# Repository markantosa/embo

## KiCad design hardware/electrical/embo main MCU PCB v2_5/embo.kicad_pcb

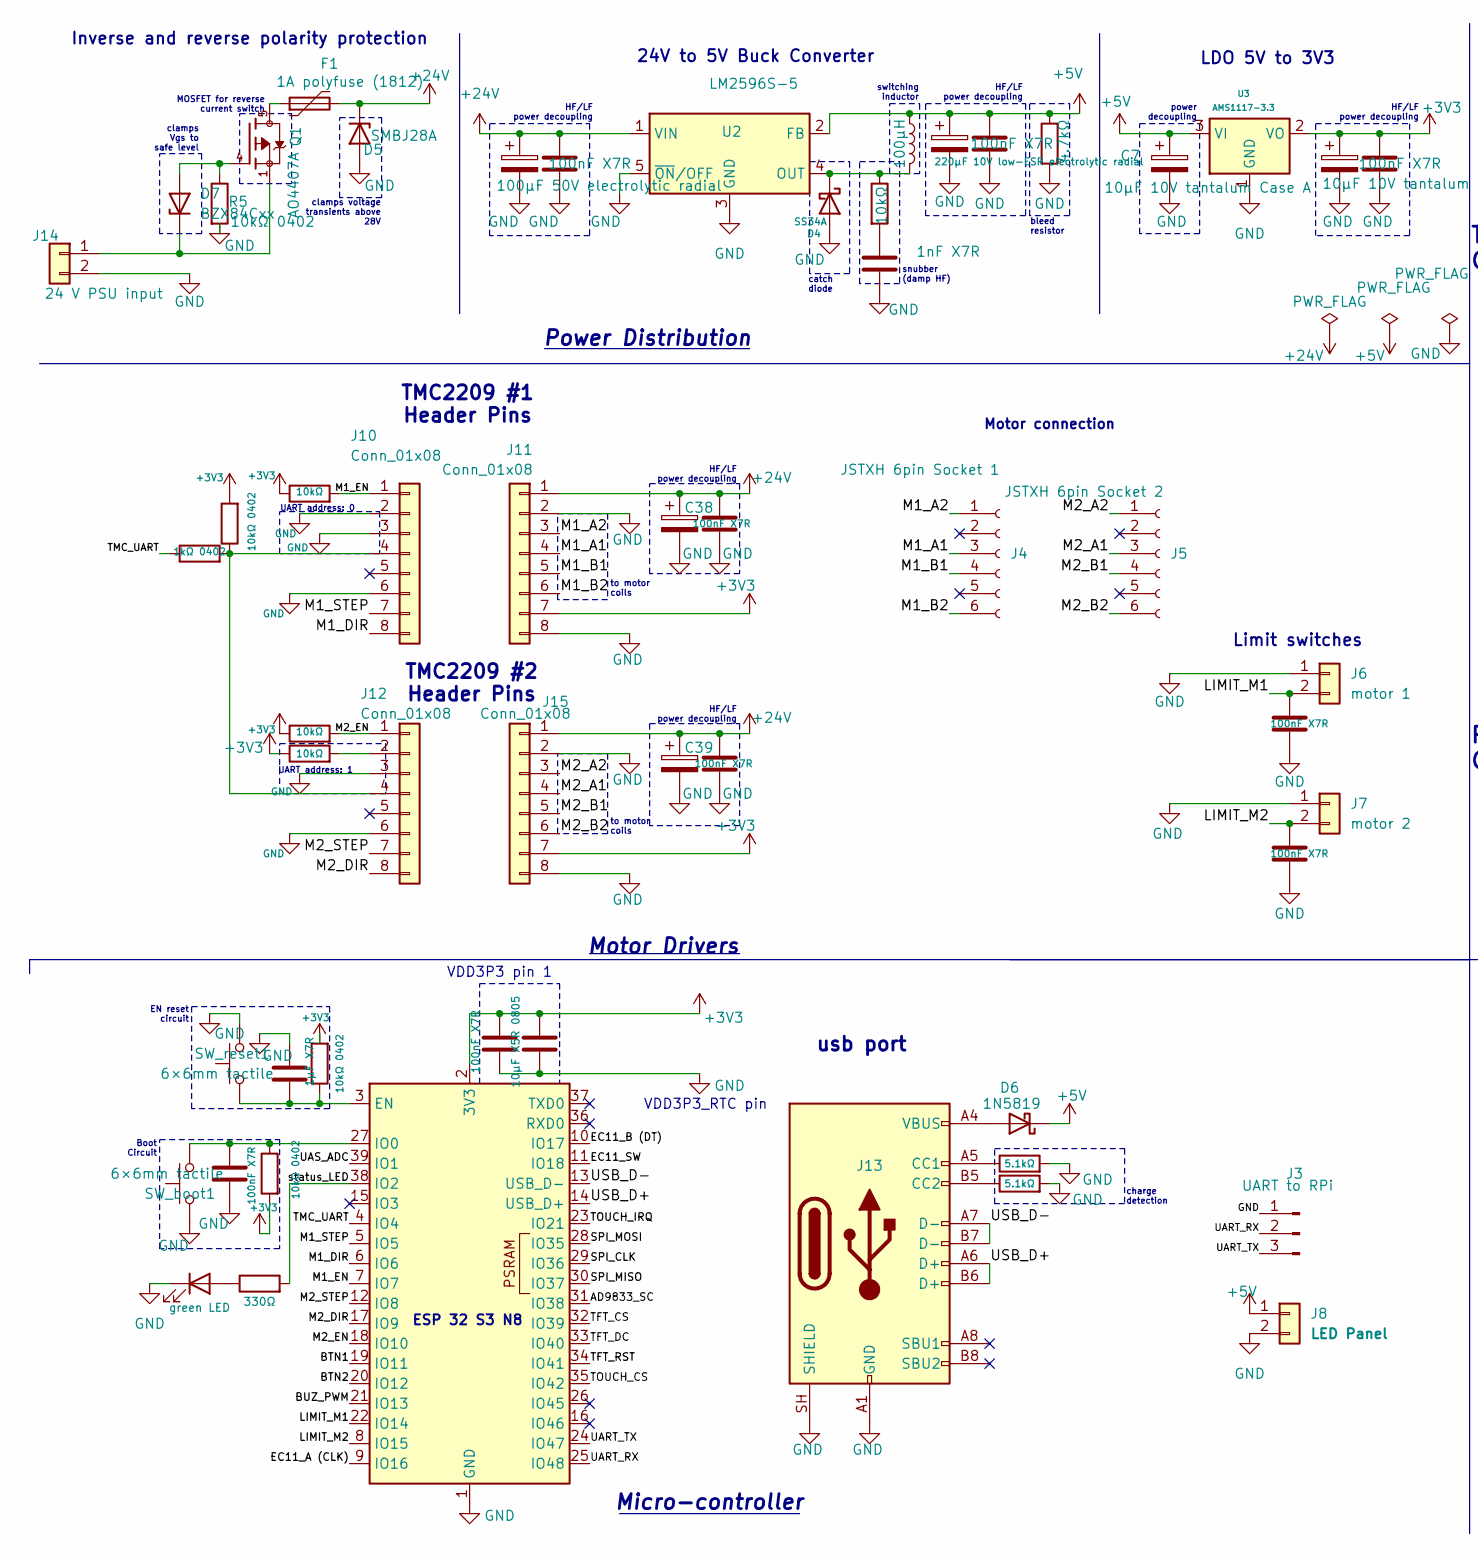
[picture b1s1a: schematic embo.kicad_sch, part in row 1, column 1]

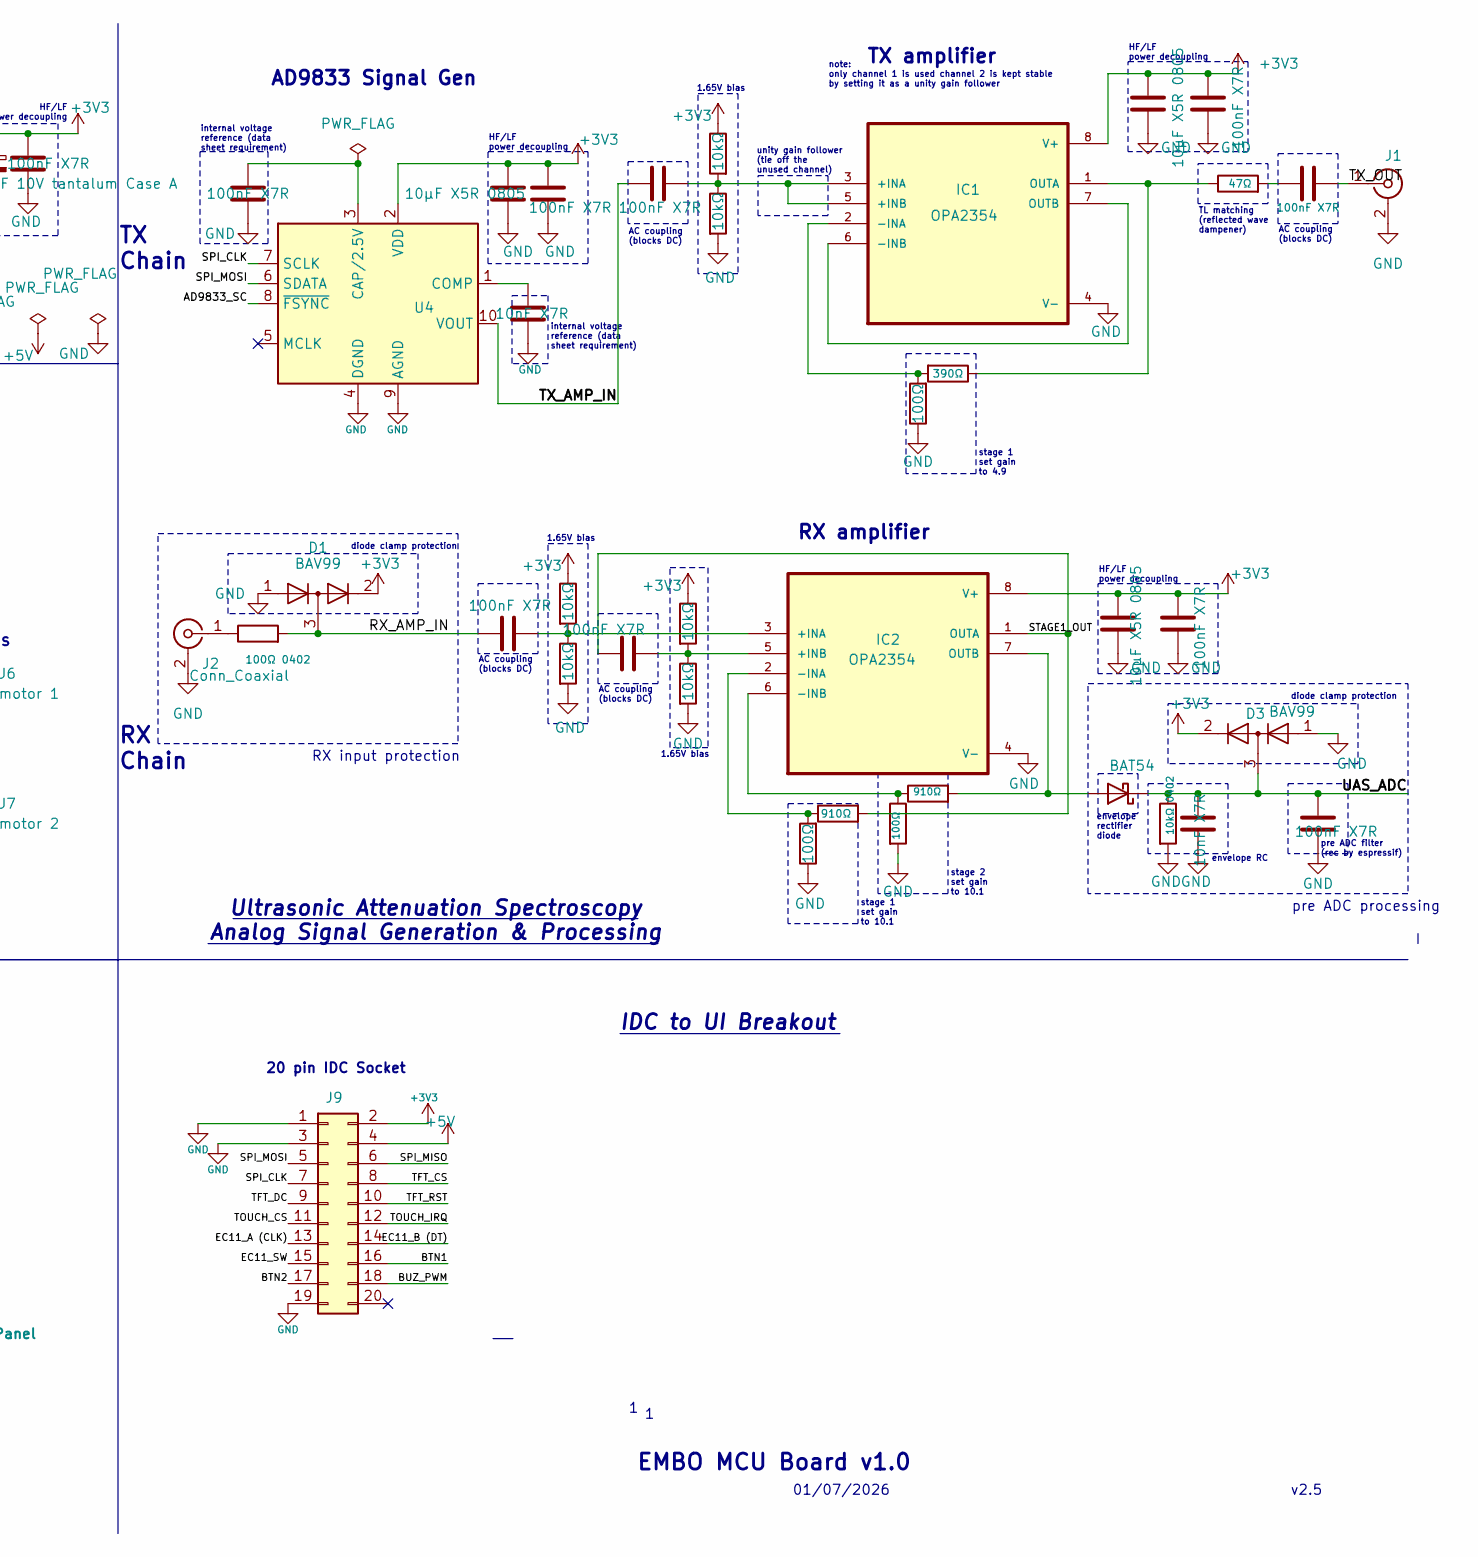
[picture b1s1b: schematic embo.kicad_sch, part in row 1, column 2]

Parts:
C7, C11: 10µF 10V tantalum Case A; CP_EIA-3216-18_Kemet-A_HandSolder
C10: 1µF X7R; C_0402_1005Metric_Pad0.74x0.62mm_HandSolder
C12, C13, C17, C18, C20, C21, C22, C23, C25, C27, C30, C31, C35, C36, C41: 100nF X7R; C_0402_1005Metric_Pad0.74x0.62mm_HandSolder
C16: 100µF 50V electrolytic radial; C_Radial_D8.0mm_H11.5mm_P3.50mm
C19: 220µF 10V low-ESR electrolytic radial; C_Radial_D8.0mm_H11.5mm_P3.50mm
C24, C26, C28, C33: 10µF X5R 0805; C_0805_2012Metric
C34: 10nF X7R; C_0402_1005Metric
C38, C39: 100µF 35V electrolytic radial; C_Radial_D6.3mm_H7.0mm_P2.50mm
C_adc1: 100nF X7R; C_0402_1005Metric_Pad0.74x0.62mm_HandSolder
C_env1: 10nF X7R; C_0402_1005Metric
Cbuck1: 100nF X7R; C_0402_1005Metric_Pad0.74x0.62mm_HandSolder
Cbuckout1: 100nF X7R; C_0402_1005Metric_Pad0.74x0.62mm_HandSolder
Csnub1: 1nF X7R; C_0402_1005Metric_Pad0.74x0.62mm_HandSolder
D1, D3: BAV99; SOT-23
D2: BAT54; D_SOD-123
D4: SS34A; D_SMA
D5: SMBJ28A; D_SMA
D6: 1N5819; D_SOD-123
D7: BZX84Cxx; SOT-23
F1: 1A polyfuse (1812); Fuse_1812_4532Metric_Pad1.30x3.40mm_HandSolder
IC1, IC2: OPA2354; SOIC-8_3.9x4.9mm_P1.27mm; DigiKey_Part_Number 296-25648-1-ND
J1, J2: Conn_Coaxial; SMA_Molex_73251-1153_EdgeMount_Horizontal
J3: UART to RPi; JST_XH_B3B-XH-A_1x03_P2.50mm_Vertical
J4: JSTXH 6pin Socket 1; JST_XH_B6B-XH-A_1x06_P2.50mm_Vertical
J5: JSTXH 6pin Socket 2; JST_XH_B6B-XH-A_1x06_P2.50mm_Vertical
J6: motor 1; JST_XH_B2B-XH-A_1x02_P2.50mm_Vertical
J7: motor 2; JST_XH_B2B-XH-A_1x02_P2.50mm_Vertical
J8: LED Panel; JST_XH_B2B-XH-A_1x02_P2.50mm_Vertical
J9: Conn_02x10_Odd_Even; IDC-Header_2x10_P2.54mm_Vertical
J10, J11, J12, J15: Conn_01x08; PinSocket_1x08_P2.54mm_Vertical
J13: USB_C_Receptacle_USB2.0_16P; USB_C_Receptacle_HRO_TYPE-C-31-M-12
J14: 24 V PSU input; TerminalBlock_Phoenix_PT-1,5-2-3.5-H_1x02_P3.50mm_Horizontal
L1: 100µH; L_Bourns_SRR1260
LED_stat1: green LED; LED_0805_2012Metric
Q1: AO4407A; SOIC-8_3.9x4.9mm_P1.27mm; PARTREV I
R1, R9, R12, R21, R22, R28, R29, R38, R39: 10kΩ; R_0402_1005Metric_Pad0.72x0.64mm_HandSolder
R5, R40, R41: 10kΩ 0402; R_0402_1005Metric_Pad0.72x0.64mm_HandSolder
R6: 330Ω; R_0402_1005Metric_Pad0.72x0.64mm_HandSolder
R17, R18: 5.1kΩ; R_0402_1005Metric_Pad0.72x0.64mm_HandSolder
R19: 4.7kΩ; R_0402_1005Metric_Pad0.72x0.64mm_HandSolder
R26, R31, R37: 100Ω; R_0402_1005Metric_Pad0.72x0.64mm_HandSolder
R27, R35: 910Ω; R_0402_1005Metric_Pad0.72x0.64mm_HandSolder
R32: 47Ω; R_0402_1005Metric_Pad0.72x0.64mm_HandSolder
R33: 390Ω; R_0402_1005Metric_Pad0.72x0.64mm_HandSolder
R_PDN_UP1: 10kΩ 0402; R_0402_1005Metric_Pad0.72x0.64mm_HandSolder
R_UART1: 1kΩ 0402; R_0402_1005Metric_Pad0.72x0.64mm_HandSolder
R_env1: 10kΩ 0402; R_0402_1005Metric_Pad0.72x0.64mm_HandSolder
R_in1: 100Ω 0402; R_0402_1005Metric_Pad0.72x0.64mm_HandSolder
Rsnub1: 10kΩ; R_0402_1005Metric_Pad0.72x0.64mm_HandSolder
SW_boot1: 6×6mm tactile; SW_SPST_EVQP2_MiddlePushTravel_H2.5mm
SW_reset1: 6×6mm tactile; SW_SPST_EVQP2_MiddlePushTravel_H2.5mm
U1: ESP32-S3-WROOM-1
U2: LM2596S-5; TO-263-5_TabPin3
U3: AMS1117-3.3; SOT-223-3_TabPin2
U4: AD9833xRM; MSOP-10_3x3mm_P0.5mm

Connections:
+3V3: C11.1, C12.1, C22.2, C23.1, C24.1, C25.1, C26.1, C28.2, C31.1, C33.2, D1.2 (A), D3.2 (A), IC1.8 (V+), IC2.8 (V+), J9.2, J11.7, J15.7, R1.1, R9.1, R12.1, R21.1, R28.1, R38.1, R40.2, R41.2, R_PDN_UP1.2, U1.2 (3V3), U3.2 (VO), U4.2 (VDD)
+5V: C7.1, C19.1, Cbuckout1.1, D6.1 (K), J8.1, J9.4, L1.1, R19.1, U2.2 (FB), U3.3 (VI)
+24V: C13.1, C16.1, C36.1, C38.1, C39.1, Cbuck1.1, D5.1 (K), F1.2, J11.1, J15.1, U2.1 (VIN)
/AD9833_SC: U1.31 (IO38), U4.8 (~FSYNC)
/BTN1: J9.16, U1.19 (IO11)
/BTN2: J9.17, U1.20 (IO12)
/BUZ_PWM: J9.18, U1.21 (IO13)
/EC11_A (CLK): J9.13, U1.9 (IO16)
/EC11_B (DT): J9.14, U1.10 (IO17)
/EC11_SW: J9.15, U1.11 (IO18)
/LIMIT_M1: C17.1, J6.2, U1.22 (IO14)
/LIMIT_M2: C18.1, J7.2, U1.8 (IO15)
/M1_A1: J4.3, J11.4
/M1_A2: J4.1, J11.3
/M1_B1: J4.4, J11.5
/M1_B2: J4.6, J11.6
/M1_DIR: J10.8, U1.6 (IO6)
/M1_EN: J10.1, R1.2, U1.7 (IO7)
/M1_STEP: J10.7, U1.5 (IO5)
/M2_A1: J5.3, J15.4
/M2_A2: J5.1, J15.3
/M2_B1: J5.4, J15.5
/M2_B2: J5.6, J15.6
/M2_DIR: J12.8, U1.17 (IO9)
/M2_EN: J12.1, R9.2, U1.18 (IO10)
/M2_STEP: J12.7, U1.12 (IO8)
/RX_AMP_IN: C20.1, D1.3 (K), R_in1.2
/SPI_CLK: J9.7, U1.29 (IO36), U4.7 (SCLK)
/SPI_MISO: J9.6, U1.30 (IO37)
/SPI_MOSI: J9.5, U1.28 (IO35), U4.6 (SDATA)
/STAGE1_OUT: C21.1, IC2.1 (OUTA), R35.2
/TFT_CS: J9.8, U1.32 (IO39)
/TFT_DC: J9.9, U1.33 (IO40)
/TFT_RST: J9.10, U1.34 (IO41)
/TMC_UART: R_UART1.1, U1.4 (IO4)
/TOUCH_CS: J9.11, U1.35 (IO42)
/TOUCH_IRQ: J9.12, U1.23 (IO21)
/TX_AMP_IN: C35.1, U4.10 (VOUT)
/TX_OUT: C27.2, J1.1 (In)
/UART_RX: J3.2, U1.25 (IO48)
/UART_TX: J3.3, U1.24 (IO47)
/UAS_ADC: C_adc1.1, C_env1.1, D2.1 (K), D3.3 (K), R_env1.1, U1.39 (IO1)
/USB_D+: J13.A6 (D+), J13.B6 (D+), U1.14 (USB_D+)
/USB_D-: J13.A7 (D-), J13.B7 (D-), U1.13 (USB_D-)
/status_LED: R6.2, U1.38 (IO2)
GND: C7.2, C10.2, C11.2, C12.2, C13.2, C16.2, C17.2, C18.2, C19.2, C22.1, C23.2, C24.2, C25.2, C26.2, C28.1, C30.2, C31.2, C33.1, C34.1, C36.2, C38.2, C39.2, C41.2, C_adc1.2, C_env1.2, Cbuck1.2, Cbuckout1.2, Csnub1.2, D1.1 (K), D3.1 (K), D4.2 (A), D5.2 (A), IC1.4 (V-), IC2.4 (V-), J1.2 (Ext), J2.2 (Ext), J3.1, J6.1, J7.1, J8.2, J9.1, J9.3, J9.19, J10.2, J10.3, J10.6, J11.2, J11.8, J12.3, J12.6, J13.A1 (GND), J13.A12 (GND), J13.B1 (GND), J13.B12 (GND), J13.SH (SHIELD), J14.2, J15.2, J15.8, LED_stat1.1 (K), R5.2, R17.2, R18.2, R19.2, R22.2, R26.1, R29.2, R31.2, R37.1, R39.2, R_env1.2, SW_boot1.2, SW_reset1.2, U1.1 (GND), U1.40 (GND), U1.41 (GND), U2.3 (GND), U2.5 (~ON/OFF), U3.1 (GND), U4.4 (DGND), U4.9 (AGND)
unnamed: C27.1, R32.2
unnamed: Csnub1.1, Rsnub1.2
unnamed: D2.2 (A), IC2.7 (OUTB), R27.2
unnamed: D4.1 (K), L1.2, Rsnub1.1, U2.4 (OUT)
unnamed: D6.2 (A), J13.A4 (VBUS), J13.A9 (VBUS), J13.B4 (VBUS), J13.B9 (VBUS)
unnamed: D7.1 (A), Q1.4, R5.1
unnamed: D7.3 (K), J14.1, Q1.1, Q1.2, Q1.3
unnamed: F1.1, Q1.5, Q1.6, Q1.7, Q1.8
unnamed: C35.2, IC1.3 (+INA), IC1.5 (+INB), R38.2, R39.1
unnamed: IC1.2 (-INA), R33.2, R37.2
unnamed: IC1.6 (-INB), IC1.7 (OUTB)
unnamed: IC1.1 (OUTA), R32.1, R33.1
unnamed: C20.2, IC2.3 (+INA), R28.2, R29.1
unnamed: C21.2, IC2.5 (+INB), R21.2, R22.1
unnamed: IC2.2 (-INA), R26.2, R35.1
unnamed: IC2.6 (-INB), R27.1, R31.1
unnamed: J2.1 (In), R_in1.1
unnamed: J10.4, J12.4, R_PDN_UP1.1, R_UART1.2
unnamed: J12.2, R12.2
unnamed: J13.A5 (CC1), R17.1
unnamed: J13.B5 (CC2), R18.1
unnamed: LED_stat1.2 (A), R6.1
unnamed: C10.1, R40.1, SW_reset1.1, U1.3 (EN)
unnamed: C41.1, R41.1, SW_boot1.1, U1.27 (IO0)
unnamed: C30.1, U4.3 (CAP/2.5V)
unnamed: C34.2, U4.1 (COMP)

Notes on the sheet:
stage 1 set gain to 4.9
pre ADC processing
HF/LF power decoupling
AD9833 Signal Gen
HF/LF power decoupling
v2.5
RX Chain
UART address: 0
ESP 32 S3 N8
note: only channel 1 is used channel 2 is kept stable by setting it as a unity gain follower
TMC2209 #2 Header Pins
RX input protection
envelope rectifier diode
EMBO MCU Board v1.0
envelope RC
AC coupling (blocks DC)
pre ADC filter (rec by espressif)
internal voltage reference (data sheet requirement)
TMC2209 #1 Header Pins
VDD3P3_RTC pin
stage 1 set gain to 10.1
LDO 5V to 3V3
unity gain follower (tie off the unused channel)
catch diode
TL matching (reflected wave dampener)
snubber (damp HF)
VDD3P3 pin 1
1.65V bias
stage 2 set gain to 10.1
to motor coils
01/07/2026
24V to 5V Buck Converter
Boot Circuit
RX amplifier
Micro-controller
TX Chain
TX amplifier
clamps voltage transients above 28V
switching inductor
power decoupling

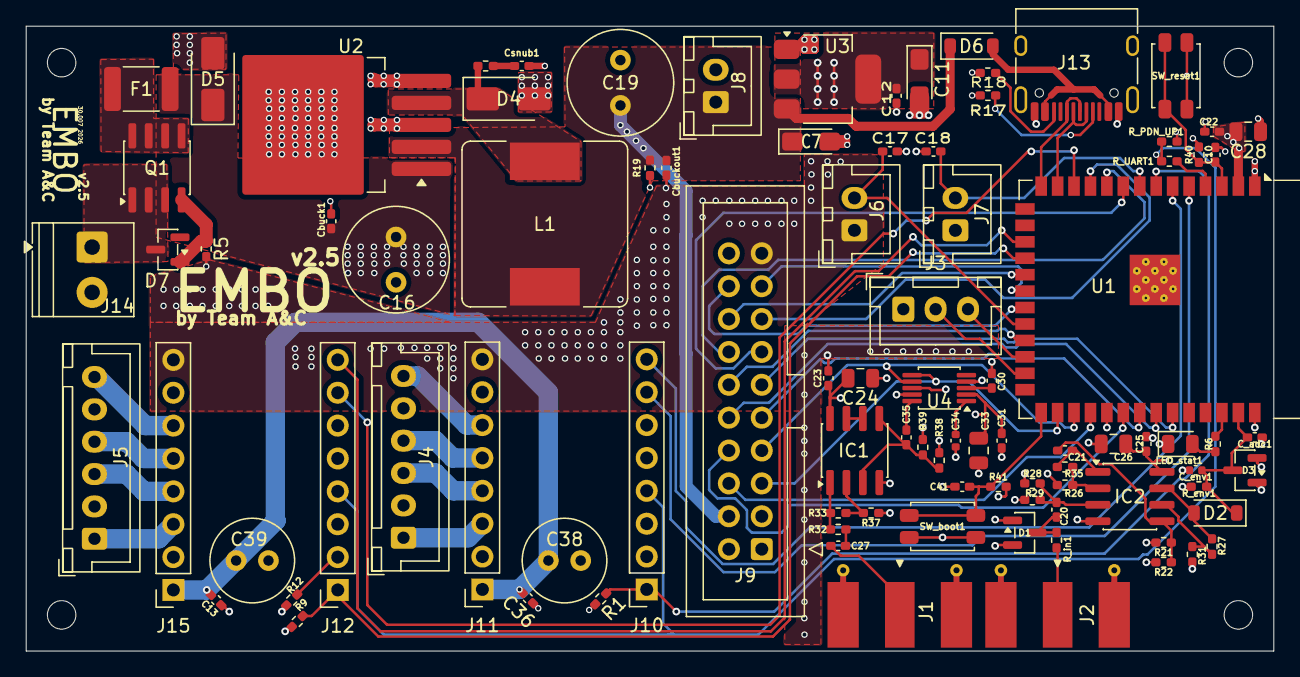
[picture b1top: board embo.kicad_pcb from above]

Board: 4 copper layers, 96.4 x 48.3 mm, 94 parts (0 on the bottom side), 72 nets.

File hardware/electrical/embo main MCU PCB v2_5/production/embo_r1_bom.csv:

Designator,Footprint,Quantity,Value,LCSC Part #
C10,0402,1,1µF X7R,
"C11, C7",CP_EIA-3216-18_Kemet-A_HandSolder,2,10µF 10V tantalum Case A,
"C12, C13, C17, C18, C20, C21, C22, C23, C25, C27, C30, C31, C35, C36, C41, CBUCK1, CBUCKOUT1, C_ADC1",0402,18,100nF X7R,
C16,C_Radial_D8.0mm_H11.5mm_P3.50mm,1,100µF 50V electrolytic radial,
C19,C_Radial_D8.0mm_H11.5mm_P3.50mm,1,220µF 10V low-ESR electrolytic radial,
"C24, C26, C28, C33",0805,4,10µF X5R 0805,
"C34, C_ENV1",0402,2,10nF X7R,
"C38, C39",C_Radial_D6.3mm_H7.0mm_P2.50mm,2,100µF 35V electrolytic radial,
CSNUB1,0402,1,1nF X7R,
"D1, D3",SOT-23,2,BAV99,
D2,D_SOD-123,1,BAT54,
D4,D_SMA,1,SS34A,
D5,D_SMA,1,SMBJ28A,
D6,D_SOD-123,1,1N5819,
D7,SOT-23,1,BZX84Cxx,
F1,1812,1,1A polyfuse (1812),
"IC1, IC2",SOIC-8_3.9x4.9mm_P1.27mm,2,OPA2354,
"J1, J2",SMA_Molex_73251-1153_EdgeMount_Horizontal,2,Conn_Coaxial,
"J10, J11, J12, J15",PinSocket_1x08_P2.54mm_Vertical,4,Conn_01x08,
J13,USB_C_Receptacle_HRO_TYPE-C-31-M-12,1,USB_C_Receptacle_USB2.0_16P,
J14,"TerminalBlock_Phoenix_PT-1,5-2-3.5-H_1x02_P3.50mm_Horizontal",1,24 V PSU input,
J3,JST_XH_B3B-XH-A_1x03_P2.50mm_Vertical,1,UART to RPi,
J4,JST_XH_B6B-XH-A_1x06_P2.50mm_Vertical,1,JSTXH 6pin Socket 1,
J5,JST_XH_B6B-XH-A_1x06_P2.50mm_Vertical,1,JSTXH 6pin Socket 2,
J6,JST_XH_B2B-XH-A_1x02_P2.50mm_Vertical,1,motor 1,
J7,JST_XH_B2B-XH-A_1x02_P2.50mm_Vertical,1,motor 2,
J8,JST_XH_B2B-XH-A_1x02_P2.50mm_Vertical,1,LED Panel,
J9,IDC-Header_2x10_P2.54mm_Vertical,1,Conn_02x10_Odd_Even,
L1,L_Bourns_SRR1260,1,100µH,
LED_STAT1,0805,1,green LED,
Q1,SOIC-8_3.9x4.9mm_P1.27mm,1,AO4407A,
"R1, R12, R21, R22, R28, R29, R38, R39, R9, RSNUB1",0402,10,10kΩ,
"R17, R18",0402,2,5.1kΩ,
R19,0402,1,4.7kΩ,
"R26, R31, R37",0402,3,100Ω,
"R27, R35",0402,2,910Ω,
R32,0402,1,47Ω,
R33,0402,1,390Ω,
"R40, R41, R5, R_ENV1, R_PDN_UP1",0402,5,10kΩ 0402,
R6,0402,1,330Ω,
R_IN1,0402,1,100Ω 0402,
R_UART1,0402,1,1kΩ 0402,
"SW_BOOT1, SW_RESET1",SW_SPST_EVQP2_MiddlePushTravel_H2.5mm,2,6×6mm tactile,
U1,ESP32-S3-WROOM-1,1,ESP32-S3-WROOM-1,
U2,TO-263-5_TabPin3,1,LM2596S-5,
U3,SOT-223-3_TabPin2,1,AMS1117-3.3,
U4,MSOP-10_3x3mm_P0.5mm,1,AD9833xRM,
